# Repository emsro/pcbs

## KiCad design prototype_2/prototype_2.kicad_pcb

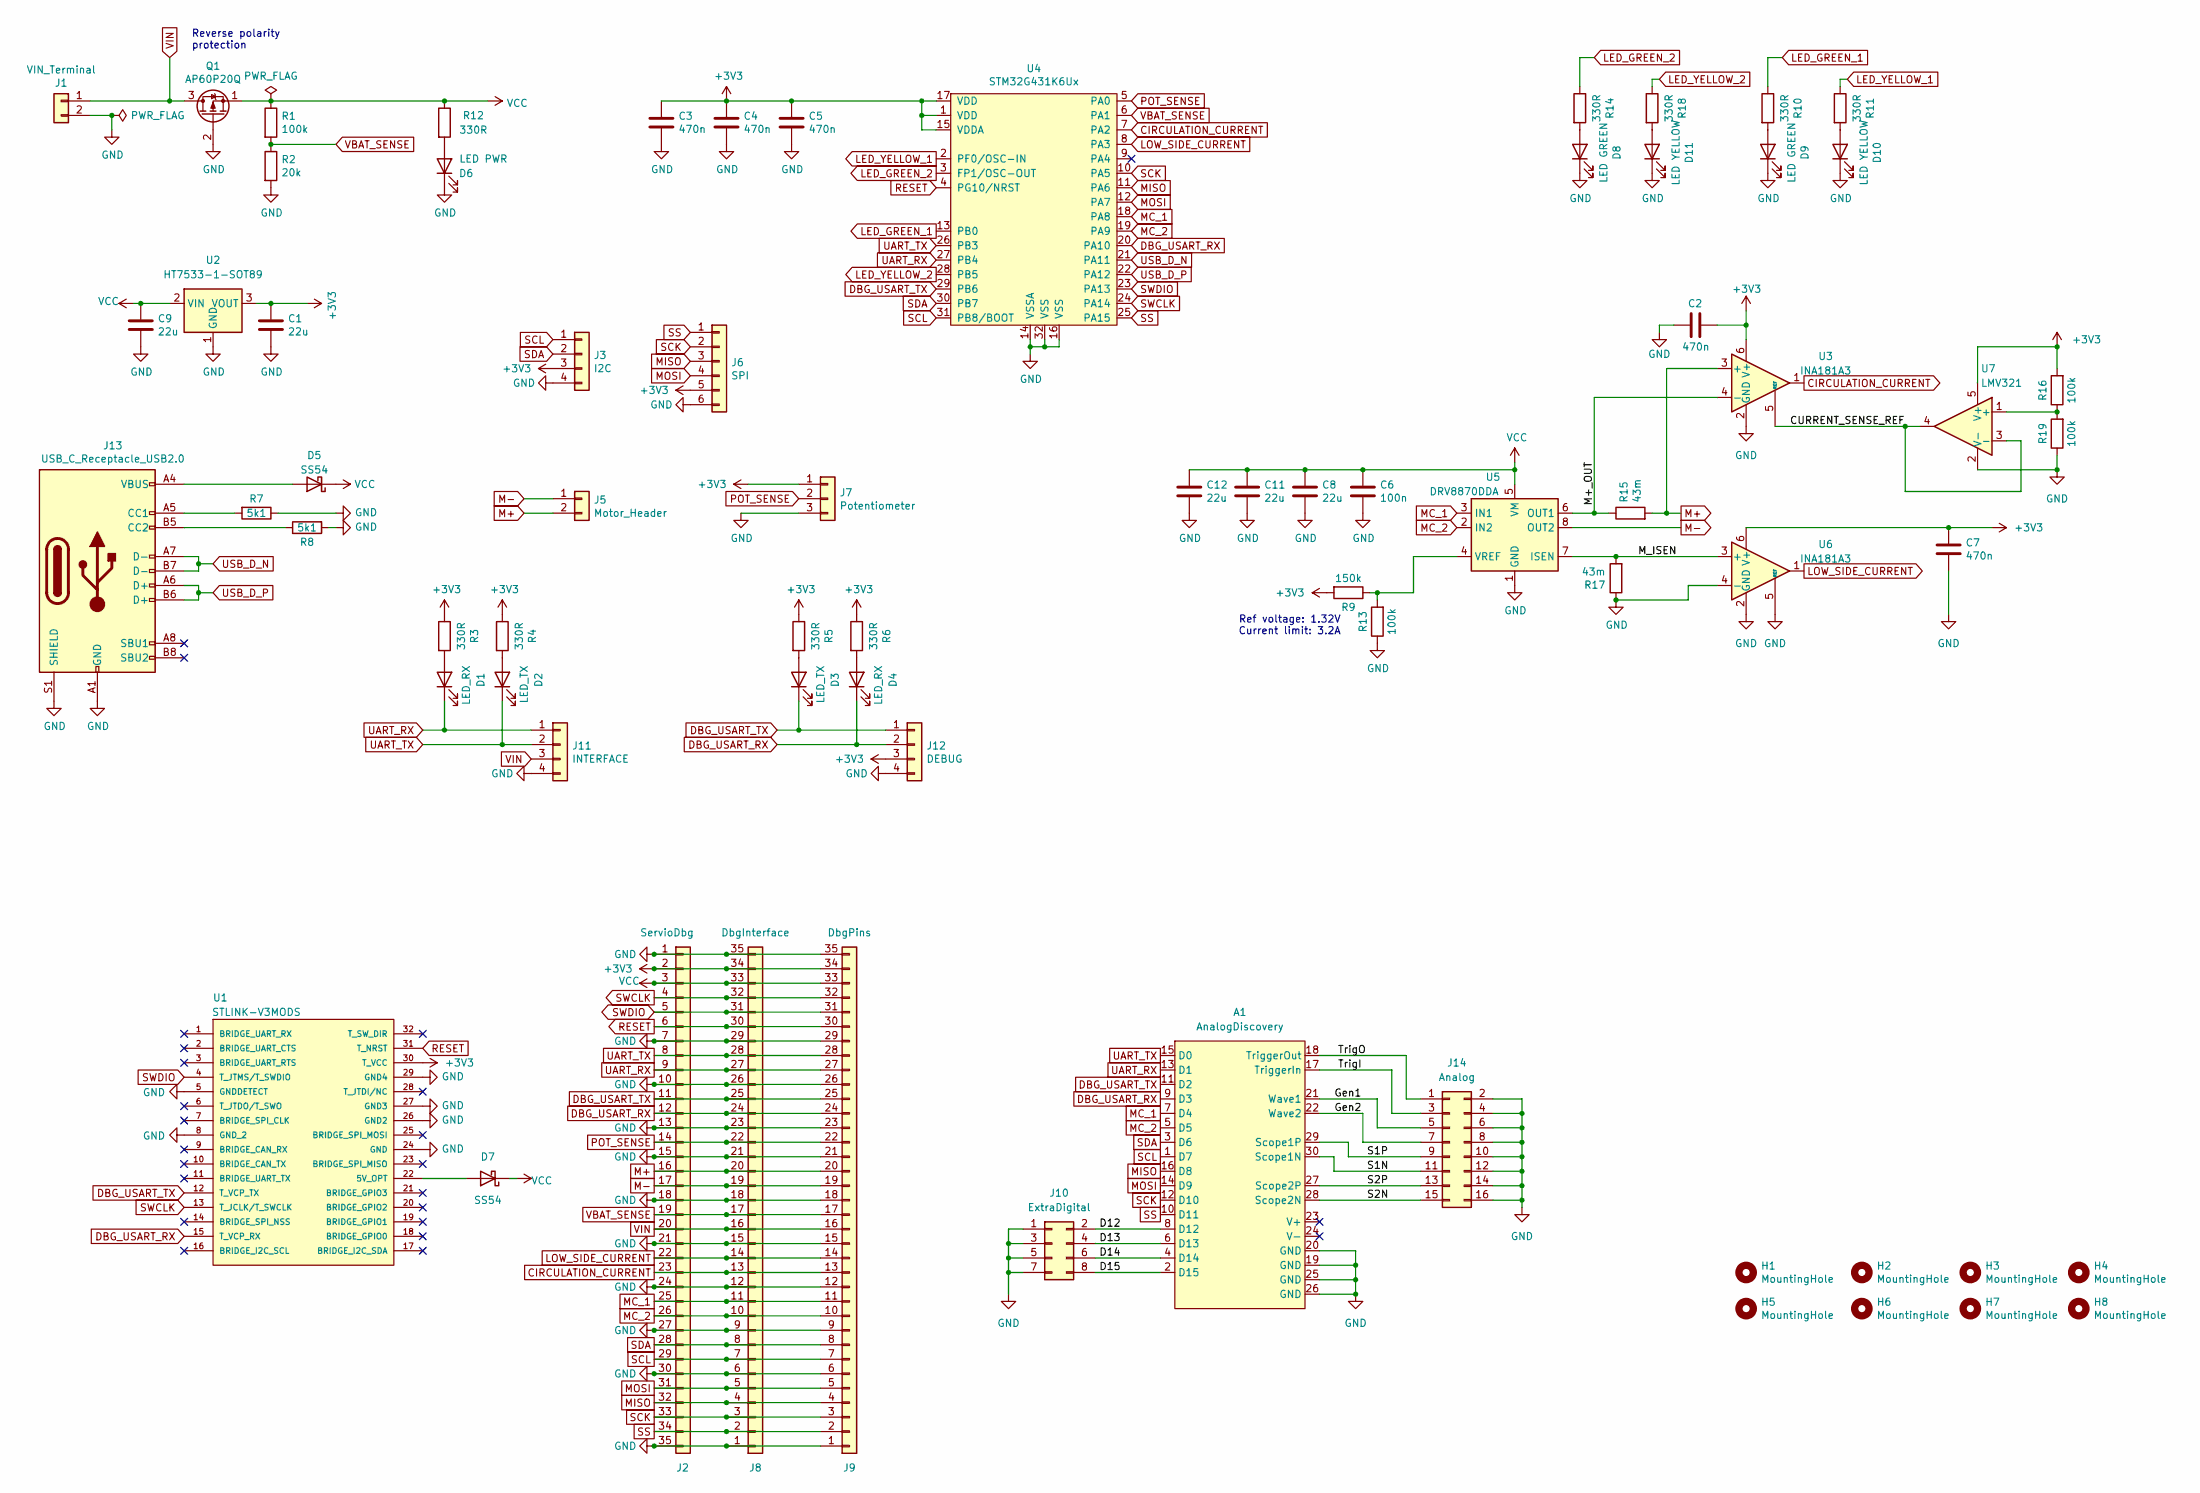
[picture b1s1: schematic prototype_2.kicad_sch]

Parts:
A1: AnalogDiscovery; PinSocket_2x15_P2.54mm_Horizontal; JLCPCB_IGNORE IGNORE
C1, C8, C9, C11, C12: 22u; C_0805_2012Metric; LCSC C2922481
C2, C3, C4, C5, C7: 470n; C_0402_1005Metric; LCSC C47339
C6: 100n; C_0603_1608Metric; LCSC C14663
D1, D4: LED_RX; LED_0603_1608Metric; LCSC C72038
D2, D3: LED_TX; LED_0603_1608Metric; LCSC C72038
D5, D7: SS54; D_SMA; LCSC C22452
D6: LED PWR; LED_0603_1608Metric; LCSC C72043
D8, D9: LED GREEN; LED_0603_1608Metric; LCSC C72043
D10, D11: LED YELLOW; LED_0603_1608Metric; LCSC C72038
H1, H2, H3, H4: MountingHole; MountingHole_3.2mm_M3; JLCPCB_IGNORE IGNORE
H5, H6, H7, H8: MountingHole; MountingHole_2.2mm_M2; JLCPCB_IGNORE IGNORE
J1: VIN_Terminal; PinHeader_1x02_P2.54mm_Horizontal; JLCPCB_IGNORE IGNORE
J2: ServioDbg; Hirose_FH12-35S-0.5SH_1x35-1MP_P0.50mm_Horizontal; LCSC C2932713
J3: I2C; PinHeader_1x04_P2.54mm_Horizontal; JLCPCB_IGNORE IGNORE
J5: Motor_Header; PinHeader_1x02_P2.54mm_Horizontal; JLCPCB_IGNORE IGNORE
J6: SPI; PinHeader_1x06_P2.54mm_Horizontal; JLCPCB_IGNORE IGNORE
J7: Potentiometer; PinHeader_1x03_P2.54mm_Horizontal; JLCPCB_IGNORE IGNORE
J8: DbgInterface; Hirose_FH12-35S-0.5SH_1x35-1MP_P0.50mm_Horizontal; LCSC C2932713
J9: DbgPins; PinHeader_2x18_P2.54mm_Vertical; JLCPCB_IGNORE IGNORE
J10: ExtraDigital; PinHeader_2x04_P2.54mm_Vertical; JLCPCB_IGNORE IGNORE
J11: INTERFACE; PinHeader_1x04_P2.54mm_Horizontal; JLCPCB_IGNORE IGNORE
J12: DEBUG; PinHeader_1x04_P2.54mm_Horizontal; JLCPCB_IGNORE IGNORE
J13: USB_C_Receptacle_USB2.0; USB_C_Female-16Pin-HPJF; LCSC C165948
J14: Analog; PinHeader_2x08_P2.54mm_Vertical; JLCPCB_IGNORE IGNORE
Q1: AP60P20Q; DFN3.3X3.3-EP; LCSC C2828591
R1, R13, R16, R19: 100k; R_0402_1005Metric; LCSC C25741
R2: 20k; R_0402_1005Metric; LCSC C25765
R3, R4, R5, R6, R10, R11, R12, R14, R18: 330R; R_0402_1005Metric; LCSC C25104
R7, R8: 5k1; R_0402_1005Metric; LCSC C25905
R9: 150k; R_0402_1005Metric; LCSC C25755
R15, R17: 43m; R_1206_3216Metric; LCSC C175772
U1: STLINK-V3MODS; MOD_STLINK-V3M_MB1467; MANUFACTURER_PART_NUMBER STLINKV3MOS; JLCPCB_IGNORE IGNORE
U2: HT7533-1-SOT89; SOT-89-3; LCSC C14289
U3, U6: INA181A3; SOT-23-6; LCSC C129285
U4: STM32G431K6Ux; STM32FG431-32; LCSC C1236625
U5: DRV8870DDA; Texas_HTSOP-8-1EP_3.9x4.9mm_P1.27mm_EP2.95x4.9mm_Mask2.4x3.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; LCSC C86590
U7: LMV321; SOT-23-5; LCSC C7972

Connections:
+3V3: C1.1, C2.2, C3.1, C4.1, C5.1, C7.1, J2.2, J3.3, J6.5, J7.1, J8.34, J9.34, J12.3, R3.1, R4.1, R5.1, R6.1, R9.2, R16.2, U1.30 (T_VCC), U2.3 (VOUT), U3.6 (V+), U4.1 (VDD), U4.15 (VDDA), U4.17 (VDD), U6.6 (V+), U7.5 (V+)
/CURRENT_SENSE_REF: U3.5 (REF), U7.3 (-), U7.4
/D12: A1.8 (D12), J10.2
/D13: A1.6 (D13), J10.4
/D14: A1.4 (D14), J10.6
/D15: A1.2 (D15), J10.8
/Gen1: A1.21 (Wave1), J14.5
/Gen2: A1.22 (Wave2), J14.7
/M+_OUT: R15.1, U3.4 (-), U5.6 (OUT1)
/M_ISEN: R17.2, U5.7 (ISEN), U6.3 (+)
/S1N: A1.30 (Scope1N), J14.11
/S1P: A1.29 (Scope1P), J14.9
/S2N: A1.28 (Scope2N), J14.15
/S2P: A1.27 (Scope2P), J14.13
/TrigI: A1.17 (TriggerIn), J14.3
/TrigO: A1.18 (TriggerOut), J14.1
CIRCULATION_CURRENT: J2.23, J8.13, J9.13, U3.1, U4.7 (PA2)
DBG_USART_RX: A1.9 (D3), D4.1 (K), J2.12, J8.24, J9.24, J12.2, U1.15 (T_VCP_RX), U4.20 (PA10)
DBG_USART_TX: A1.11 (D2), D3.1 (K), J2.11, J8.25, J9.25, J12.1, U1.12 (T_VCP_TX), U4.29 (PB6)
GND: A1.19 (GND), A1.20 (GND), A1.25 (GND), A1.26 (GND), C1.2, C2.1, C3.2, C4.2, C5.2, C6.2, C7.2, C8.2, C9.2, C11.2, C12.2, D6.1 (K), D8.1 (K), D9.1 (K), D10.1 (K), D11.1 (K), J1.2, J2.1, J2.7, J2.10, J2.13, J2.15, J2.18, J2.21, J2.24, J2.27, J2.30, J2.35, J3.4, J6.6, J7.3, J8.1, J8.6, J8.9, J8.12, J8.15, J8.18, J8.21, J8.23, J8.26, J8.29, J8.35, J9.1, J9.6, J9.9, J9.12, J9.15, J9.18, J9.21, J9.23, J9.26, J9.29, J9.35, J10.1, J10.3, J10.5, J10.7, J11.4, J12.4, J13.A1 (GND), J13.A12 (GND), J13.B1 (GND), J13.B12 (GND), J13.S1 (SHIELD), J14.2, J14.4, J14.6, J14.8, J14.10, J14.12, J14.14, J14.16, Q1.2 (G), R2.2, R7.1, R8.2, R13.1, R17.1, R19.1, U1.5 (GNDDETECT), U1.8 (GND_2), U1.24 (GND), U1.26 (GND2), U1.27 (GND3), U1.29 (GND4), U2.1 (GND), U3.2 (GND), U4.14 (VSSA), U4.16 (VSS), U4.32 (VSS), U5.1 (GND), U5.9 (GND), U6.2 (GND), U6.4 (-), U6.5 (REF), U7.2 (V-)
LED_GREEN_1: R10.1, U4.13 (PB0)
LED_GREEN_2: R14.1, U4.3 (FP1/OSC-OUT)
LED_YELLOW_1: R11.1, U4.2 (PF0/OSC-IN)
LED_YELLOW_2: R18.1, U4.28 (PB5)
LOW_SIDE_CURRENT: J2.22, J8.14, J9.14, U4.8 (PA3), U6.1
M+: J2.16, J5.2, J8.20, J9.20, R15.2, U3.3 (+)
M-: J2.17, J5.1, J8.19, J9.19, U5.8 (OUT2)
MC_1: A1.7 (D4), J2.25, J8.11, J9.11, U4.18 (PA8), U5.3 (IN1)
MC_2: A1.5 (D5), J2.26, J8.10, J9.10, U4.19 (PA9), U5.2 (IN2)
MISO: A1.16 (D8), J2.32, J6.3, J8.4, J9.4, U4.11 (PA6)
MOSI: A1.14 (D9), J2.31, J6.4, J8.5, J9.5, U4.12 (PA7)
unnamed: D1.2 (A), R3.2
unnamed: D2.2 (A), R4.2
unnamed: D3.2 (A), R5.2
unnamed: D4.2 (A), R6.2
unnamed: D5.2 (A), J13.A4 (VBUS), J13.A9 (VBUS), J13.B4 (VBUS), J13.B9 (VBUS)
unnamed: D6.2 (A), R12.2
unnamed: D7.2 (A), U1.22 (5V_OPT)
unnamed: D8.2 (A), R14.2
unnamed: D9.2 (A), R10.2
unnamed: D10.2 (A), R11.2
unnamed: D11.2 (A), R18.2
unnamed: J13.A5 (CC1), R7.2
unnamed: J13.B5 (CC2), R8.1
unnamed: R9.1, R13.2, U5.4 (VREF)
unnamed: R16.1, R19.2, U7.1 (+)
POT_SENSE: J2.14, J7.2, J8.22, J9.22, U4.5 (PA0)
RESET: J2.6, J8.30, J9.30, U1.31 (T_NRST), U4.4 (PG10/NRST)
SCK: A1.12 (D10), J2.33, J6.2, J8.3, J9.3, U4.10 (PA5)
SCL: A1.1 (D7), J2.29, J3.1, J8.7, J9.7, U4.31 (PB8/BOOT)
SDA: A1.3 (D6), J2.28, J3.2, J8.8, J9.8, U4.30 (PB7)
SS: A1.10 (D11), J2.34, J6.1, J8.2, J9.2, U4.25 (PA15)
SWCLK: J2.4, J8.32, J9.32, U1.13 (T_JCLK/T_SWCLK), U4.24 (PA14)
SWDIO: J2.5, J8.31, J9.31, U1.4 (T_JTMS/T_SWDIO), U4.23 (PA13)
UART_RX: A1.13 (D1), D1.1 (K), J2.9, J8.27, J9.27, J11.1, U4.27 (PB4)
UART_TX: A1.15 (D0), D2.1 (K), J2.8, J8.28, J9.28, J11.2, U4.26 (PB3)
USB_D_N: J13.A7 (D-), J13.B7 (D-), U4.21 (PA11)
USB_D_P: J13.A6 (D+), J13.B6 (D+), U4.22 (PA12)
VBAT_SENSE: J2.19, J8.17, J9.17, R1.2, R2.1, U4.6 (PA1)
VCC: C6.1, C8.1, C9.1, C11.1, C12.1, D5.1 (K), D7.1 (K), J2.3, J8.33, J9.33, Q1.1 (S), R1.1, R12.1, U2.2 (VIN), U5.5 (VM)
VIN: J1.1, J2.20, J8.16, J9.16, J11.3, Q1.3 (D)

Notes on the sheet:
Ref voltage: 1.32V Current limit: 3.2A
Reverse polarity protection

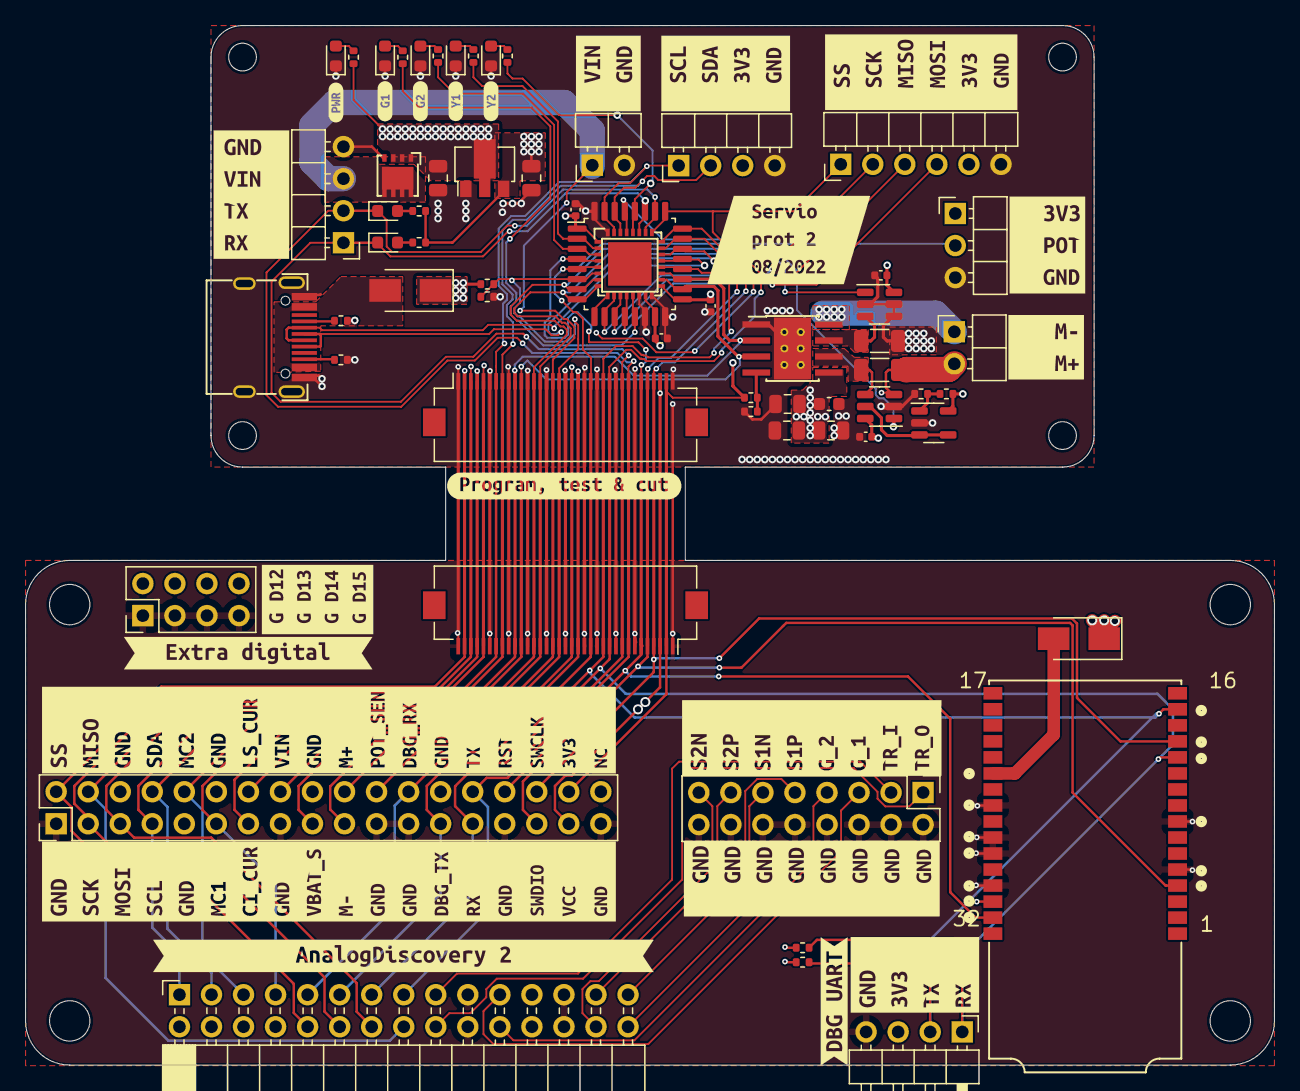
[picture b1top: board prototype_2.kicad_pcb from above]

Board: 4 copper layers, 99.0 x 82.4 mm, 93 parts (0 on the bottom side), 61 nets.

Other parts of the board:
kibuzzard-62F78A97: G***; kibuzzard-62F78A97
kibuzzard-62F78AC2: G***; kibuzzard-62F78AC2
kibuzzard-62F78AD0: G***; kibuzzard-62F78AD0
kibuzzard-62F78AE4: G***; kibuzzard-62F78AE4
kibuzzard-62F78AEF: G***; kibuzzard-62F78AEF
kibuzzard-62F78BE6: G***; kibuzzard-62F78BE6
kibuzzard-62F78C8F: G***; kibuzzard-62F78C8F
kibuzzard-62F78C24: G***; kibuzzard-62F78C24
kibuzzard-62F78CD0: G***; kibuzzard-62F78CD0
kibuzzard-62F78D02: G***; kibuzzard-62F78D02
kibuzzard-62F78D38: G***; kibuzzard-62F78D38
kibuzzard-62F78D92: G***; kibuzzard-62F78D92
kibuzzard-62F753A1: G***; kibuzzard-62F753A1
kibuzzard-62F755BE: G***; kibuzzard-62F755BE
kibuzzard-62F756CA: G***; kibuzzard-62F756CA
kibuzzard-62F760DB: G***; kibuzzard-62F760DB
kibuzzard-62F7521F: G***; kibuzzard-62F7521F
kibuzzard-62F7549B: G***; kibuzzard-62F7549B
kibuzzard-62F7568E: G***; kibuzzard-62F7568E
kibuzzard-62F75303: G***; kibuzzard-62F75303
kibuzzard-62F75565: G***; kibuzzard-62F75565
kibuzzard-62F75722: G***; kibuzzard-62F75722

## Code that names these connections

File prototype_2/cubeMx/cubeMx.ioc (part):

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Mcu.Name=STM32G030F6Px
Mcu.Package=TSSOP20
Mcu.UserName=STM32G030F6Px
PA0.Mode=IN0
PA0.Signal=ADC1_IN0
PA1.Mode=IN1
PA1.Signal=ADC1_IN1
PA13.Mode=Serial_Wire
PA13.Signal=SYS_SWDIO
PA14-BOOT0.Mode=Serial_Wire
PA14-BOOT0.Signal=SYS_SWCLK
PA2.Mode=Asynchronous
PA2.Signal=USART2_TX
PA3.Mode=Asynchronous
PA3.Signal=USART2_RX
PA6.Signal=S_TIM3_CH1
PA7.Signal=S_TIM17_CH1
PA8.Signal=S_TIM1_CH1
PB6.Mode=IrDA
PB6.Signal=USART1_TX
PB7.Mode=IrDA
PB7.Signal=USART1_RX
PB9.Mode=INFRARED
PB9.Signal=IR_OUT
RCC.HSE_VALUE=8000000
RCC.SYSCLKFreq_VALUE=16000000
board=custom

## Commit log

2023-07-13 added pro2 design
